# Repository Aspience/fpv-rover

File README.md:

# FPV Rover

Monorepo for an FPV rover (LEGO Audi e-tron) controlled from a web UI with live video, telemetry OSD, and optional physical gamepad input.

## Contents

- [Overview](#overview)
- [Hardware requirements](#hardware-requirements)
- [KiCad project](#kicad-project)
- [Software requirements](#software-requirements)
- [Installation and updates](#installation-and-updates)
  - [Prerequisites on the Pi](#prerequisites-on-the-pi)
  - [First install (bootstrap)](#first-install-bootstrap)
  - [Updating to a new version](#updating-to-a-new-version)
- [Technical reference](#technical-reference)
  - [Repository structure](#repository-structure)
  - [Backend modules](#backend-modules)
  - [Environment variables](#environment-variables)
  - [Local development](#local-development)
  - [Backend ↔ frontend sync](#backend--frontend-sync)
  - [Infra / Docker](#infra--docker)
  - [Releasing a new version](#releasing-a-new-version)
  - [Boot persistence (optional)](#boot-persistence-optional)

---

## Overview

The project follows a **modular architecture**: each hardware capability (motion, power, thermal, IMU, light, camera, gamepad) is an independent backend module under `backend/modules/<name>/`. Gamepads connect over USB or **Bluetooth** (the `bluetooth` module handles wireless pairing; `gamepad` reads input via evdev). Modules are toggled at runtime via `ROVER_MODULES_*` feature flags in `.env` — only enabled modules are loaded, initialized, and exposed to the UI.

This design lets you **mix and match hardware configurations** without changing application code. A minimal bench setup might enable only `camera` and `motion`; a fully instrumented rover can enable every sensor. The frontend reads module flags from `GET /config` on startup and shows or hides controls accordingly.

The stack runs on **Raspberry Pi** (reference build: Pi Zero 2 W) inside Docker Compose: FastAPI backend, React SPA, nginx reverse proxy, MediaMTX for WebRTC video, and a pigpio sidecar for GPIO/PWM motor control.

---

## Hardware requirements

The reference rover is built around a **Raspberry Pi** (64-bit). Peripherals connect over the buses listed below.

| Component | Module / role | Bus / interface |
|-----------|---------------|-----------------|
| **Raspberry Pi Zero 2 W** (or compatible Pi 3/4/5) | Host — runs Docker stack | — |
| **Arducam IMX462** (Pivariety) | FPV camera, night mode | **CSI-2** → libcamera / V4L2 (`/dev/video0`) |
| **GY-302** (BH1750) | Ambient light sensor; triggers camera night mode below threshold | **I2C** (default address `0x23`) |
| **DS18B20** | Temperature sensors (motors, BMS, BEC, charger) | **1-Wire** (default GPIO 4 via `dtoverlay=w1-gpio`) |
| **TB6612FNG** × 3 | Motor drivers — front drive, rear drive, steering (LEGO Control+ hubs) | **GPIO / PWM** via pigpio daemon; encoder tachos on GPIO |
| **GY-521** (MPU6050) | Gyroscope + accelerometer (orientation OSD) | **I2C** (default address `0x68`) |
| **INA219** | Battery voltage and current monitoring | **I2C** (default address `0x40`) |
| **BMS 2S** battery charge controller | 2S Li-ion pack — **2P2S** layout (four 18650 cells) | Passive power path; temperature via DS18B20 on 1-Wire |
| **iFlight Micro 2–8S BEC** | Switched regulator — 5 V supply for the Pi | Power only (no data bus) |
| **TOF400C** | Laser ToF distance sensor | **I2C** (planned; not yet implemented in software) |
| **Gamepad** (USB or Bluetooth) | Physical input (optional); **Bluetooth** is used to pair wireless controllers, then input is read via evdev | **Bluetooth** (pairing, host netns via `nsenter`) → **evdev** (`/dev/input/event*`) |

### Host interfaces to enable

Before deployment, enable these on the Pi (see [Prerequisites on the Pi](#prerequisites-on-the-pi)):

| Interface | Used by |
|-----------|---------|
| I2C (`/dev/i2c-1`) | INA219, BH1750, MPU6050, TOF400C |
| 1-Wire (`/sys/bus/w1`) | DS18B20 |
| GPIO / pigpio (`/dev/gpiochip0`) | TB6612FNG motor drivers |
| CSI camera + Arducam overlay | IMX462 |
| Bluetooth | Gamepad pairing (wireless controllers) |
| evdev (`/dev/input`) | Gamepad input (USB and paired Bluetooth) |

Motion and gamepad modules require the **pigpiod** Docker sidecar. Without pigpio or when the daemon is unreachable, motion falls back to mock hardware (useful for local dev).

---

## KiCad project

Electrical design lives in [`hardware/`](hardware/) as a **KiCad 10** project. The schematic captures the wiring described in [`SCHEMA.md`](SCHEMA.md) (main board + expansion board buses, power path, motor drivers, sensors); `SCHEMA.md` remains the physical wiring source of truth.

| File | What it is |
|------|------------|
| `hardware/fpv-rover.kicad_pro` | KiCad project — open this in KiCad |
| `hardware/fpv-rover.kicad_sch` | Schematic (editable source) |
| `hardware/fpv-rover.kicad_pcb` | PCB layout (placeholder — build uses perfboard, see `SCHEMA.md`) |
| `hardware/fpv-rover-schematic.pdf` | Exported schematic — view without KiCad |
| `hardware/fpv-rover-schematic.svg` / `.png` | Same schematic as vector / raster image |

To view the design, open the PDF/SVG exports. To edit, open `fpv-rover.kicad_pro` in [KiCad](https://www.kicad.org/) 10+ and re-export the PDF/SVG afterwards so the rendered files stay in sync.

---

## Software requirements

| Requirement | Notes |
|-------------|-------|
| **Linux 64-bit** | Required for production images and MediaMTX arm64 build |
| **Raspberry Pi OS Lite 64-bit** (recommended) | Bookworm or Trixie; Bullseye supported on Pi 4 and older |
| **Docker Engine** + **Docker Compose** plugin | Production deployment and OTA updates |
| **git**, **curl** | Bootstrap and OTA scripts |

For local development on any OS: Python 3.12+ with [uv](https://docs.astral.sh/uv/), Node.js 20+ for the frontend.

---

## Installation and updates

On Raspberry Pi, backend, frontend, and mediamtx images are built in GitHub Actions (arm64) and pulled at runtime — no local `npm run build` or `docker compose build` on the device.

### Prerequisites on the Pi

Bootstrap requires **git**, **curl**, **Docker**, and the **Docker Compose** plugin. On a fresh Raspberry Pi OS image these are often missing.

#### 1. Git and curl

```bash
sudo apt update
sudo apt install -y git curl
```

#### 2. Docker and Docker Compose

```bash
curl -fsSL https://get.docker.com | sh
sudo usermod -aG docker "$USER"
newgrp docker
```

Log out and back in (or run `newgrp docker`) so your user can run Docker without `sudo`.

Verify:

```bash
docker --version
docker compose version
docker ps
```

#### 3. I2C and 1-Wire

Backend expects `/dev/i2c-1` and `/sys/bus/w1` on the host. Enable both before bootstrap — sensors do not need to be connected yet.

```bash
sudo raspi-config
# Interface Options → I2C → Enable
# Interface Options → 1-Wire → Enable
sudo reboot
```

Or add to `/boot/firmware/config.txt` (older images: `/boot/config.txt`):

```
dtparam=i2c_arm=on
dtoverlay=w1-gpio,gpiopin=4
```

After reboot, verify:

```bash
ls /dev/i2c-1
ls /sys/bus/w1
```

`gpiopin=4` matches the default `ROVER_W1_GPIO=4` in `.env.example`.

#### 4. Arducam IMX462 camera drivers

The IMX462 is an **Arducam Pivariety** module. It requires Arducam's custom libcamera stack and a device-tree overlay on the host (outside Docker). Follow the [Arducam Pivariety Quick Start Guide](https://docs.arducam.com/Raspberry-Pi-Camera/Pivariety-Camera/Quick-Start-Guide/).

**Step 1 — download the install script:**

```bash
wget -O install_pivariety_pkgs.sh https://github.com/ArduCAM/Arducam-Pivariety-V4L2-Driver/releases/download/install_script/install_pivariety_pkgs.sh
chmod +x install_pivariety_pkgs.sh
```

**Step 2 — install Arducam libcamera (on the Pi host, before or after bootstrap):**

```bash
./install_pivariety_pkgs.sh -p libcamera_dev
./install_pivariety_pkgs.sh -p libcamera_apps
```

No reboot yet — proceed to Step 3.

**Step 3 — enable the camera overlay** in `/boot/firmware/config.txt` (Pi 4/5 Bookworm/Trixie; older images may use `/boot/config.txt`):

```
camera_auto_detect=0
dtoverlay=arducam-pivariety
```

On Pi 5 / CM5 with the camera on the **CAM0** port, use `dtoverlay=arducam-pivariety,cam0` instead.

Save and reboot:

```bash
sudo reboot
```

**Verify** after reboot:

```bash
rpicam-still --list-cameras    # Bookworm / Trixie
# or: libcamera-still --list-cameras   # Bullseye
ls /dev/video0
```

The MediaMTX container ships with Arducam libcamera libraries baked in ([`infra/mediamtx/Dockerfile`](infra/mediamtx/Dockerfile)); the **host overlay and libcamera packages** are still required for the camera device node to appear.

> If you see `Configuration file 'arducam-pivariety.json' not found for IPA module 'rpi/pisp'`, it can be safely ignored — the config is embedded in camera firmware.

#### 5. SSH deploy key

Bootstrap can generate one interactively, or configure manually:

```bash
ssh-keygen -t ed25519 -f ~/.ssh/fpv_rover_deploy -N ""
cat ~/.ssh/fpv_rover_deploy.pub
```

Add the public key in GitHub → **Settings → Deploy keys** (read-only).

`~/.ssh/config`:

```sshconfig
Host github.com
  IdentityFile ~/.ssh/fpv_rover_deploy
  IdentitiesOnly yes
```

#### 6. GHCR login (only if images are private)

```bash
echo "$GITHUB_PAT" | docker login ghcr.io -u YOUR_GITHUB_USER --password-stdin
```

PAT needs `read:packages`. Public GHCR packages do not require login.

### First install (bootstrap)

```bash
sudo mkdir -p /opt/fpv-rover && sudo chown "$USER" /opt/fpv-rover
git clone git@github.com:Aspience/fpv-rover.git /opt/fpv-rover
cd /opt/fpv-rover
./scripts/bootstrap.sh --enable-systemd
# or pin a release tag:
./scripts/bootstrap.sh --tag v0.1.5 --enable-systemd
```

Bootstrap creates `.env` from `.env.example` with production values (`ROVER_OTA_ENABLED=true`, `VITE_RPI_HOST`, `IMAGE_TAG`, etc.). It does **not** create `.env.local`.

Before pulling images, bootstrap **pauses** so you can edit env interactively (opens `${EDITOR:-nano}` on request). Set module flags, confirm `VITE_RPI_HOST`, and optionally create `.env.local` for hardware IDs — then press Enter to continue.

Example `.env.local` (do **not** copy the full `.env.example` — `.env.local` overrides `.env` and would reset OTA settings to example defaults):

```
ROVER_MODULES_MOTION_ENABLED=true
ROVER_MODULES_GAMEPAD_ENABLED=true
ROVER_MODULES_CAMERA_ENABLED=true
ROVER_THERMAL_SENSOR_IDS={"motor_steering":"28-..."}
```

Use `--non-interactive` to skip the env edit pause when env is preconfigured.

#### Bootstrap options

| Flag | Default | Description |
|------|---------|-------------|
| `--install-dir PATH` | `/opt/fpv-rover` | Install path on the device |
| `--tag TAG` | `latest` (or `$IMAGE_TAG`) | Git tag and Docker image tag to deploy |
| `--repo URL` | `git@github.com:Aspience/fpv-rover.git` | Git remote for clone/fetch |
| `--non-interactive` | off | Fail fast if SSH/GitHub/GHCR setup is missing |
| `--skip-clone` | off | Skip clone when repo is already in `--install-dir` |
| `--skip-ssh` | off | Skip SSH key generation and GitHub deploy-key prompt |
| `--skip-ghcr-login` | off | Skip `docker login ghcr.io` |
| `--skip-deploy` | off | Setup only (env, clone) — no `compose pull/up` |
| `--enable-systemd` | off | Install and enable `infra/systemd/fpv-rover.service` |
| `--quiet` | off | Less stdout; log file stays verbose |

| Env var | Used for |
|---------|----------|
| `VITE_RPI_HOST` | Browser-facing Pi IP/hostname (non-interactive bootstrap) |
| `IMAGE_TAG` | Default tag when `--tag` is omitted |
| `GHCR_USER` + `GHCR_TOKEN` | Optional GHCR login (public packages skip this) |

**Logs:** `/opt/fpv-rover/logs/bootstrap.log`

```bash
tail -100 /opt/fpv-rover/logs/bootstrap.log
```

### Updating to a new version

#### From the UI

Open **Settings** → **Check for updates** → **Install update**. The UI shows a fullscreen overlay while the rover restarts and polls `GET /health` every 3 seconds until the backend is back.

Requires `ROVER_OTA_ENABLED=true` (set by bootstrap on production installs).

#### Manual update / rollback (OTA script)

```bash
cd /opt/fpv-rover
./scripts/ota_update.sh v0.2.0        # upgrade (prompts for confirmation)
./scripts/ota_update.sh v0.1.0        # rollback (prompts for confirmation)
./scripts/ota_update.sh v0.2.0 --yes  # skip the confirmation prompt
```

The script waits 3 seconds (so the API can respond), fetches the git tag, resolves per-service image tags from `image-tags.env` (with nearest-tag fallback for older releases), pulls Docker images, and runs `docker compose up -d`. It never overwrites `.env` or `.env.local`.

Before any destructive step the script asks:

```text
Update from v0.1.0 to v0.2.0? [y/N]
```

The prompt is skipped when running non-interactively (backend OTA API), with `--yes`/`-y`, or when `ROVER_OTA_ASSUME_YES=1`.

**Logs:** `/opt/fpv-rover/logs/ota.log`

```bash
tail -100 /opt/fpv-rover/logs/ota.log
```

---

## Technical reference

### Repository structure

```
fpv-rover/
├── backend/          # Python — FastAPI, hardware modules, WebSocket
│   ├── api/          # REST routes, WebSocket handler, command/telemetry schemas
│   ├── core/         # Settings, event bus, module registry, startup
│   ├── modules/      # Pluggable hardware modules (see below)
│   └── tests/
├── frontend/         # React SPA — live video, OSD, motion levers, settings
├── infra/            # Nginx reverse proxy, MediaMTX, systemd unit
├── scripts/          # Bootstrap and OTA update scripts
├── .env.example      # Shared environment template (backend + frontend)
└── docker-compose.yml
```

Each backend module typically has `*.module.py`, `*.schema.py`, `*.config.py`, and optional `*.utils.py` / `*.service.py`.

### Backend modules

| Module | Role |
|--------|------|
| `motion` | LEGO Control+ drive (front/rear) + steering via TB6612FNG + pigpio; PID closed loop, homing calibration |
| `gamepad` | Physical gamepad over Linux evdev (`/dev/input`); maps to motion commands |
| `power` | INA219 battery monitoring (I2C) |
| `thermal` | DS18B20 temperature sensors (1-Wire) |
| `imu` | MPU6050 orientation (I2C) |
| `light` | BH1750 ambient lux (I2C); triggers camera night mode below threshold |
| `camera` | MediaMTX integration — recording and stream config |
| `bluetooth` | Bluetooth gamepad pairing (host netns via `nsenter`) |

When `ROVER_MODULES_MOTION_ENABLED=true`, the backend runs **steering calibration automatically** on startup (`core/startup.py`). Physical gamepad input requires both `ROVER_MODULES_GAMEPAD_ENABLED` and `ROVER_MODULES_MOTION_ENABLED`.

Motion tuning constants (PID loop rate, homing power, throttle limits) live in `motion.config.py`. Gamepad evdev codes and poll intervals — in `gamepad.config.py`. GPIO pins, PID gains, and speed limits are runtime settings via `ROVER_*` env.

### Environment variables

Both backend and frontend read from a **single root `.env` file**:

```bash
cp .env.example .env
```

On the Pi or in Docker, optional `.env.local` overrides `.env` without touching git-tracked files.

#### Feature flags

| Variable | Default | Description |
|----------|---------|-------------|
| `ROVER_MODULES_POWER_ENABLED` | `false` | INA219 power module |
| `ROVER_MODULES_MOTION_ENABLED` | `false` | Motion module (LEGO Control+ + TB6612FNG) |
| `ROVER_MODULES_GAMEPAD_ENABLED` | `false` | Physical gamepad via evdev |
| `ROVER_MODULES_THERMAL_ENABLED` | `false` | DS18B20 thermal module |
| `ROVER_MODULES_IMU_ENABLED` | `false` | MPU6050 IMU module |
| `ROVER_MODULES_LIGHT_ENABLED` | `false` | BH1750 light module |
| `ROVER_MODULES_CAMERA_ENABLED` | `false` | MediaMTX camera integration |
| `ROVER_MODULES_BLUETOOTH_ENABLED` | `false` | Bluetooth gamepad pairing |

Backend loads `ROVER_*` via pydantic-settings (`backend/core/config.py`).  
Frontend loads `VITE_*` via Vite with `envDir` pointing at the repo root (`frontend/vite.config.ts`).

> **Note:** `VITE_*` variables are embedded at **build time**. After changing them, rebuild the frontend (`npm run build` or `docker compose build frontend`).

#### Motion & pigpio

| Variable | Default | Description |
|----------|---------|-------------|
| `ROVER_PIGPIO_HOST` | `pigpiod` | pigpio daemon hostname (Docker service name) |
| `ROVER_PIGPIO_PORT` | `8888` | pigpio daemon TCP port |
| `ROVER_MOTION_FRONT_PWMA_GPIO` | `18` | Front drive — PWM pin (TB6612FNG PWMA) |
| `ROVER_MOTION_FRONT_AIN1_GPIO` | `23` | Front drive — direction AIN1 |
| `ROVER_MOTION_FRONT_AIN2_GPIO` | `24` | Front drive — direction AIN2 |
| `ROVER_MOTION_FRONT_TACHO_A_GPIO` | `17` | Front drive — encoder channel A |
| `ROVER_MOTION_FRONT_TACHO_B_GPIO` | `27` | Front drive — encoder channel B |
| `ROVER_MOTION_REAR_PWMA_GPIO` | `12` | Rear drive — PWM pin |
| `ROVER_MOTION_REAR_AIN1_GPIO` | `16` | Rear drive — direction AIN1 |
| `ROVER_MOTION_REAR_AIN2_GPIO` | `20` | Rear drive — direction AIN2 |
| `ROVER_MOTION_REAR_TACHO_A_GPIO` | `5` | Rear drive — encoder channel A |
| `ROVER_MOTION_REAR_TACHO_B_GPIO` | `6` | Rear drive — encoder channel B |
| `ROVER_MOTION_STEER_PWMA_GPIO` | `13` | Steering — PWM pin |
| `ROVER_MOTION_STEER_AIN1_GPIO` | `19` | Steering — direction AIN1 |
| `ROVER_MOTION_STEER_AIN2_GPIO` | `26` | Steering — direction AIN2 |
| `ROVER_MOTION_STEER_TACHO_A_GPIO` | `21` | Steering — encoder channel A |
| `ROVER_MOTION_STEER_TACHO_B_GPIO` | `22` | Steering — encoder channel B |
| `ROVER_MOTION_MAX_SPEED_TICKS` | `800` | Max drive speed in encoder ticks/s at full throttle |
| `ROVER_MOTION_STEER_MAX_DEG` | `45` | Maximum steering angle (°) |
| `ROVER_MOTION_PID_KP` | `0.8` | PID proportional gain |
| `ROVER_MOTION_PID_KI` | `0.05` | PID integral gain |
| `ROVER_MOTION_PID_KD` | `0.01` | PID derivative gain |

#### Global backend

| Variable | Default | Description |
|----------|---------|-------------|
| `ROVER_LOG_LEVEL` | `INFO` | Logging level |
| `ROVER_HOST` | `0.0.0.0` | FastAPI bind address |
| `ROVER_PORT` | `8000` | FastAPI port |
| `ROVER_I2C_BUS` | `1` | Linux I2C bus number |
| `ROVER_W1_GPIO` | `4` | 1-Wire GPIO pin (must match `dtoverlay=w1-gpio`) |
| `ROVER_WS_TELEMETRY_HZ` | `20` | WebSocket telemetry broadcast rate (Hz) |
| `ROVER_HEARTBEAT_TIMEOUT_SEC` | `1.0` | Watchdog heartbeat timeout |
| `ROVER_IO_RETRY_DELAY_SEC` | `2.0` | Hardware I/O retry delay |

#### MediaMTX

| Variable | Default | Description |
|----------|---------|-------------|
| `ROVER_MEDIAMTX_API_URL` | `http://mediamtx:9997` | MediaMTX control API |
| `ROVER_MEDIAMTX_RECORD_START_PATH` | `/v3/recordings/start/{stream_path}` | Start recording API path template |
| `ROVER_MEDIAMTX_RECORD_STOP_PATH` | `/v3/recordings/stop/{stream_path}` | Stop recording API path template |
| `ROVER_MEDIAMTX_STREAM_CONFIG_PATH` | `/v3/config/paths/patch/{stream_path}` | Patch stream config path template |
| `ROVER_MEDIAMTX_STREAM_CONFIG_GET_PATH` | `/v3/config/paths/get/{stream_path}` | Get stream config path template |

#### Hardware addresses & devices

| Variable | Default | Description |
|----------|---------|-------------|
| `ROVER_POWER_I2C_ADDRESS` | `0x40` | INA219 I2C address |
| `ROVER_IMU_I2C_ADDRESS` | `0x68` | MPU6050 I2C address |
| `ROVER_LIGHT_I2C_ADDRESS` | `0x23` | BH1750 I2C address |
| `ROVER_W1_BASE_PATH` | `/sys/bus/w1/devices` | 1-Wire sysfs base path |
| `ROVER_THERMAL_W1_SLAVE_FILE` | `w1_slave` | Filename inside each sensor directory |
| `ROVER_THERMAL_SENSOR_IDS` | *(JSON map)* | DS18B20 ROM IDs keyed by sensor name |
| `ROVER_CAMERA_V4L2_DEVICE` | `/dev/video0` | Camera V4L2 device |
| `ROVER_CAMERA_V4L2_CTL_BIN` | `v4l2-ctl` | Path to `v4l2-ctl` binary |
| `ROVER_CAMERA_STREAM_PATH` | `rover` | MediaMTX stream path name |

#### Frontend (build-time)

| Variable | Default | Description |
|----------|---------|-------------|
| `VITE_RPI_HOST` | `localhost` | Dev server proxy target; production WebRTC fallback |
| `VITE_API_PORT` | `8000` | Dev server proxy target for REST/WebSocket |
| `VITE_WEBRTC_PORT` | `8889` | MediaMTX WebRTC (WHEP) port in the browser |

#### Docker / OTA (production)

| Variable | Default | Description |
|----------|---------|-------------|
| `ROVER_OTA_ENABLED` | `false` | Allow `POST /update/apply` (set `true` on Pi) |
| `ROVER_OTA_INSTALL_DIR` | `/opt/fpv-rover` | Install path on the device |
| `ROVER_OTA_SCRIPT` | `/opt/fpv-rover/scripts/ota_update.sh` | Update script path |
| `ROVER_OTA_SSH_KEY_PATH` | *(empty)* | Deploy key path; bootstrap sets `$HOME/.ssh/fpv_rover_deploy` |
| `ROVER_OTA_ASSUME_YES` | *(empty)* | Set `1`/`true` to skip manual-update confirmation |
| `ROVER_GITHUB_OWNER` | `aspience` | GitHub owner for release check and GHCR image path |
| `ROVER_GITHUB_REPO` | `fpv-rover` | GitHub repo for release check and GHCR image path |
| `ROVER_GITHUB_TOKEN` | *(empty)* | Optional PAT for GitHub API rate limits |
| `FPV_ROVER_IMAGE_REGISTRY` | `ghcr.io` | Container registry for production images |
| `IMAGE_TAG` | `latest` | Target release tag for git checkout and app version |
| `BACKEND_IMAGE_TAG` | *(auto)* | Pin backend image tag — override in `.env.local` |
| `FRONTEND_IMAGE_TAG` | *(auto)* | Pin frontend image tag — override in `.env.local` |
| `MEDIAMTX_IMAGE_TAG` | *(auto)* | Pin mediamtx image tag — override in `.env.local` |

> **Per-service tag precedence:** on deploy/OTA, tags are resolved as (1) explicit pin in `.env.local`, then (2) `image-tags.env` from the checked-out release, then (3) nearest existing GHCR tag. To pin a specific service tag, put it in `.env.local` (not `.env`, which the OTA script rewrites).

Compose also uses `PIGPIOD_IMAGE` (default `zinen2/alpine-pigpiod:pigpio-v79`) for the GPIO sidecar.

Production images are pulled from `${FPV_ROVER_IMAGE_REGISTRY}/${ROVER_GITHUB_OWNER}/${ROVER_GITHUB_REPO}-{backend,frontend,mediamtx}`.

### Local development

#### Backend

```bash
uv sync --project backend
uv run --project backend pytest
uv run --project backend ruff check
uv run --project backend ruff format
uv run --project backend fpv-rover
```

API: `http://localhost:8000` — OpenAPI docs at `/docs`.

Install pre-commit hooks (from repo root):

```bash
uv run --project backend pre-commit install
```

#### Frontend

React 19 SPA: live video (WebRTC), telemetry OSD, on-screen throttle/steer levers, keyboard shortcuts, light and camera controls. Physical gamepads are handled on the **backend** (evdev).

**Stack:** React 19, TypeScript, Vite 8, Tailwind CSS 4, Zustand, Zod, Axios.

```bash
cd frontend
npm ci
npm run dev          # http://localhost:5173
npm run build        # production bundle → dist/
npm run lint
npm run preview
```

Run backend and frontend in separate terminals:

```bash
# terminal 1
uv run --project backend fpv-rover

# terminal 2
cd frontend && npm run dev
```

Vite proxies `/api` and `/ws` to the backend using `VITE_RPI_HOST` and `VITE_API_PORT`.

### Backend ↔ frontend sync

The UI talks to the backend over three channels. Keep their contracts aligned when you change either side.

#### 1. Shared configuration (`.env`)

Module flags (`ROVER_MODULES_*`) are exposed via `GET /config`; the frontend fetches them on startup.

When deploying on a Pi or via Docker, REST and WebSocket use nginx on port 80 (`/api`, `/ws`). WebRTC/WHEP uses `window.location.hostname` and `VITE_WEBRTC_PORT` (not proxied through nginx).

#### 2. REST — module flags

| | Backend | Frontend |
|---|---------|----------|
| Endpoint | `GET /config` | `fetchConfig()` in `frontend/src/api/http.ts` |
| Schema | `backend/core/schemas/config.py` → `ConfigResponse` | `frontend/src/types/schemas.ts` → `ConfigResponseSchema` |
| Types | OpenAPI (`/openapi.json`) | `frontend/src/types/contracts.ts` |

**After changing the REST API:**

1. Update Pydantic models in `backend/modules/<name>/<name>.schema.py` or `backend/core/schemas/`.
2. Run `uv run --project backend pytest`.
3. Mirror the shape in `frontend/src/types/schemas.ts` (Zod) and `frontend/src/types/contracts.ts`.
4. Optionally regenerate REST types (backend must be running): `cd frontend && npm run generate:api`

#### 3. WebSocket — telemetry and commands

| | Backend | Frontend |
|---|---------|----------|
| Endpoint | `WS /ws` | `frontend/src/api/websocket.ts` |
| Server → client | `backend/modules/<name>/<name>.schema.py`, `backend/api/schemas/telemetry.py` | `TelemetryMessageSchema`, `ErrorMessageSchema` |
| Client → server | `backend/api/schemas/commands.py` | `ClientCommandSchema` |

**Message types:**

- **Telemetry** (default 20 Hz): `{ type: "telemetry", modules: { power?, motion?, light?, thermal?, imu?, bluetooth?, gamepad? } }`
- **Commands (frontend):** `heartbeat` (every 500 ms), `move`, `calibrate`, `set_brightness`
- **Commands (backend only today):** `record` — not yet sent from the UI
- **Errors:** `{ type: "error", message: string }`

Motion control from the UI, keyboard, or physical gamepad converges on the same backend path. Use `GET /ws-protocol` on a running backend to inspect documented JSON shapes.

> **Note:** `STEER_MAX_DEG` in `frontend/src/constants.ts` is hardcoded (default 45°). Keep it aligned with `ROVER_MOTION_STEER_MAX_DEG` when you change steering limits.

#### 4. Video — WebRTC (WHEP)

Video does not go through FastAPI. MediaMTX serves the stream; the frontend connects via WHEP:

- Stream path: `rover` (see `infra/mediamtx/mediamtx.yml`)
- Frontend: `POST http://{host}:{VITE_WEBRTC_PORT}/rover/whep`
- Backend camera module controls recording via `ROVER_MEDIAMTX_API_URL`

Keep `VITE_WEBRTC_PORT` aligned with MediaMTX `webrtcAddress` (default **8889**).

#### Sync checklist

When you add or change an API field:

- [ ] Pydantic model in `backend/modules/<name>/<name>.schema.py` (or `backend/api/schemas/`)
- [ ] Zod schema in `frontend/src/types/schemas.ts`
- [ ] TypeScript interface in `frontend/src/types/contracts.ts` (if applicable)
- [ ] Backend tests (`pytest`)
- [ ] Manual check: backend running + `npm run dev` or built frontend

### Infra / Docker

```bash
cp .env.example .env
docker compose up --build
```

| Service | Port(s) | Role |
|---------|---------|------|
| `pigpiod` | 8888 (internal) | pigpio daemon — GPIO/PWM for motion motors |
| `backend` | 8000 | FastAPI, hardware modules |
| `frontend` | 3000 | Static SPA (Caddy) |
| `nginx` | 80 | Reverse proxy: `/` → frontend, `/api/` and `/ws` → backend |
| `mediamtx` | 8554, 8889, 8189/udp, 9997 | RTSP, WebRTC, ICE UDP, control API (Arducam/Pivariety libcamera) |

Pi device mounts in [`docker-compose.yml`](docker-compose.yml): `/dev/i2c-1`, `/dev/video0`, `/dev/input` (gamepad), `/sys/bus/w1` (1-Wire), `/dev/gpiochip0` (pigpiod sidecar).

Production UI on port 80: REST → `/api`, WebSocket → `/ws`. WebRTC/WHEP → `http://<pi-ip>:8889/rover/whep`.

Locally, `mediamtx` is built from [`infra/mediamtx/Dockerfile`](infra/mediamtx/Dockerfile); production pulls a pre-built image from GHCR.

### Releasing a new version

```bash
git tag v0.2.0
git push origin v0.2.0
```

GitHub Actions (`.github/workflows/release.yml`) builds arm64 backend, frontend, and mediamtx images and pushes them to GHCR. Each service is rebuilt **only when its context changed** since the previous `v*` tag. Skipped services keep their previous image tag.

The workflow writes `image-tags.env` with resolved tags per service. Release assets include `image-tags.env`, compose files, `infra/**/*`, OTA/bootstrap scripts, and `.env.example`.

### Boot persistence (optional)

Bootstrap can install the systemd unit with `--enable-systemd`, or manually:

```bash
sudo cp infra/systemd/fpv-rover.service /etc/systemd/system/
sudo systemctl enable --now fpv-rover
```

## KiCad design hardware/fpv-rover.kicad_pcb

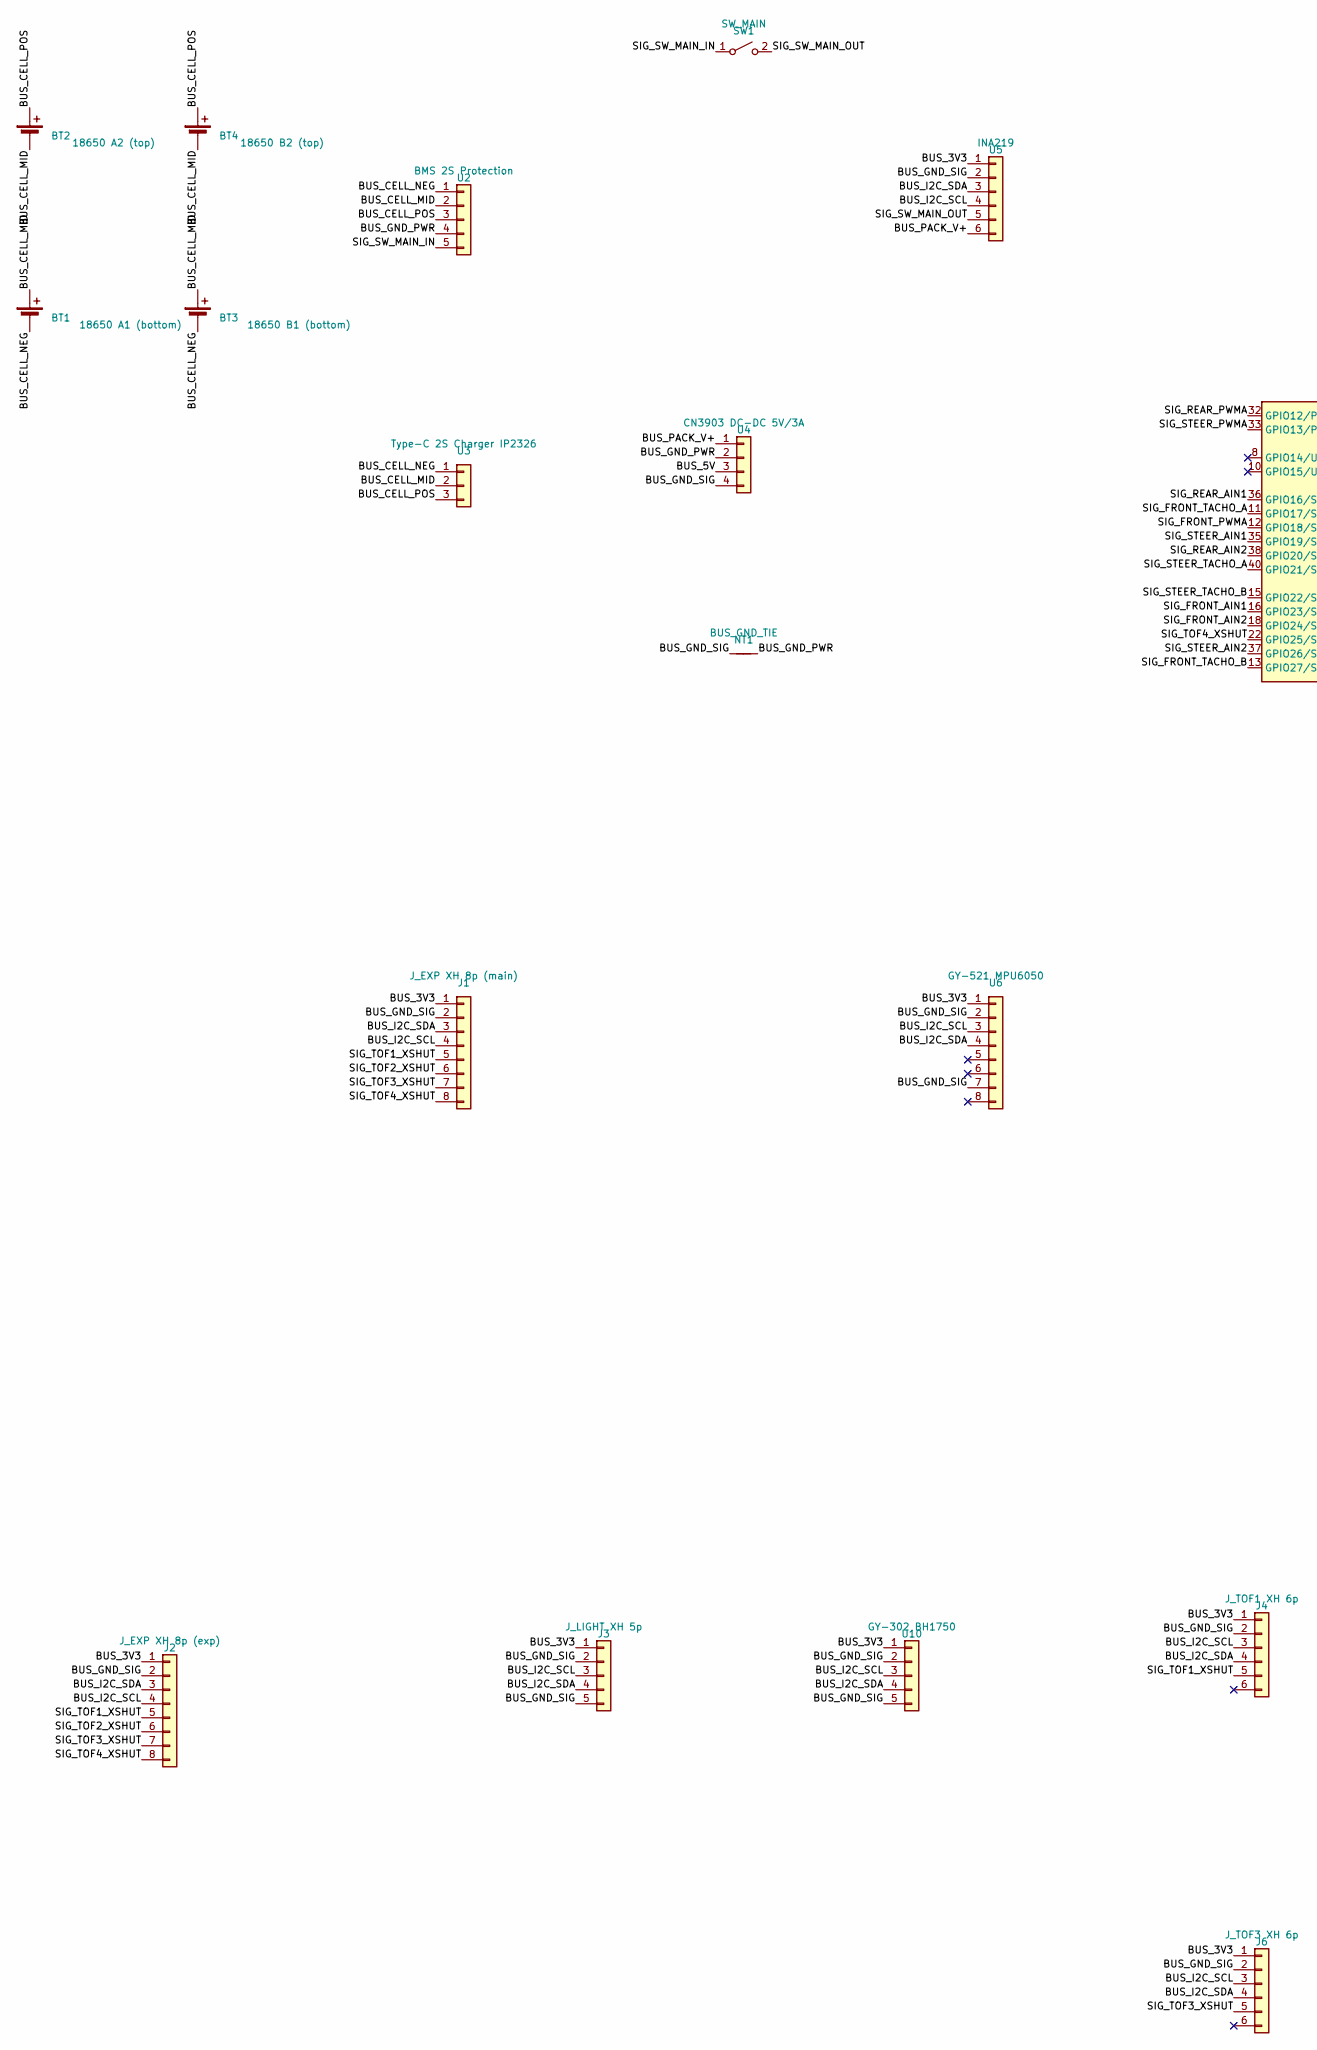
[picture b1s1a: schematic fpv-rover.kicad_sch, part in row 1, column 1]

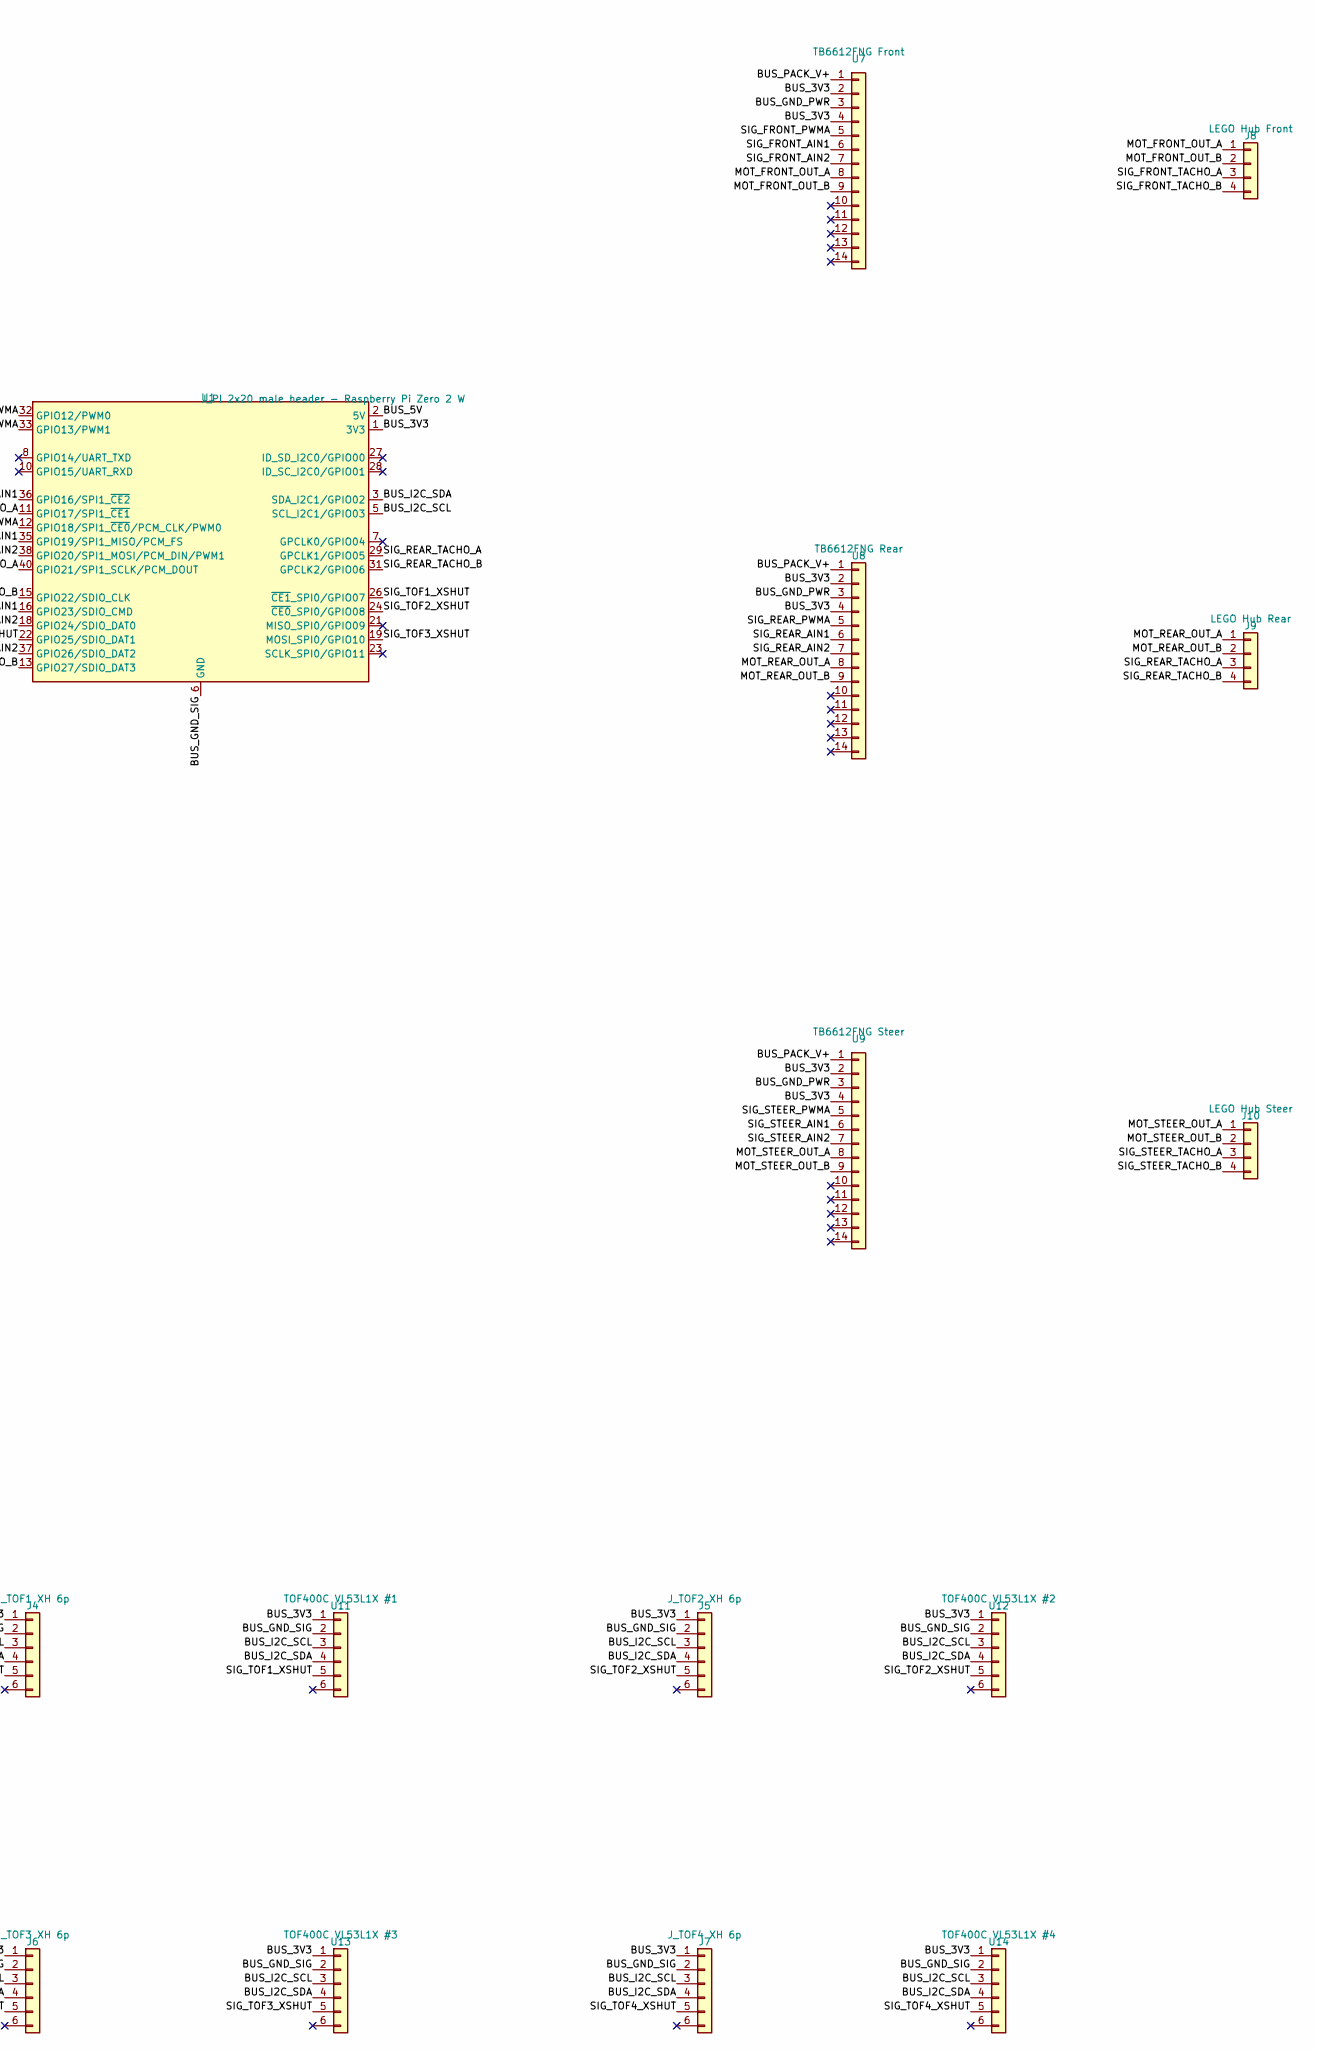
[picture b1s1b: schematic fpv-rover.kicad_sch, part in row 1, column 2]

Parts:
BT1: 18650 A1 (bottom); PinHeader_1x02_P2.54mm_Vertical
BT2: 18650 A2 (top); PinHeader_1x02_P2.54mm_Vertical
BT3: 18650 B1 (bottom); PinHeader_1x02_P2.54mm_Vertical
BT4: 18650 B2 (top); PinHeader_1x02_P2.54mm_Vertical
J1: J_EXP XH 8p (main); JST_XH_B8B-XH-A_1x08_P2.50mm_Vertical
J2: J_EXP XH 8p (exp); JST_XH_B8B-XH-A_1x08_P2.50mm_Vertical
J3: J_LIGHT XH 5p; JST_XH_B5B-XH-A_1x05_P2.50mm_Vertical
J4: J_TOF1 XH 6p; JST_XH_B6B-XH-A_1x06_P2.50mm_Vertical
J5: J_TOF2 XH 6p; JST_XH_B6B-XH-A_1x06_P2.50mm_Vertical
J6: J_TOF3 XH 6p; JST_XH_B6B-XH-A_1x06_P2.50mm_Vertical
J7: J_TOF4 XH 6p; JST_XH_B6B-XH-A_1x06_P2.50mm_Vertical
J8: LEGO Hub Front; JST_XH_B4B-XH-A_1x04_P2.50mm_Vertical
J9: LEGO Hub Rear; JST_XH_B4B-XH-A_1x04_P2.50mm_Vertical
J10: LEGO Hub Steer; JST_XH_B4B-XH-A_1x04_P2.50mm_Vertical
NT1: BUS_GND_TIE; NetTie-2_THT_Pad1.0mm
SW1: SW_MAIN; PinHeader_1x02_P2.54mm_Vertical
U1: J_PI 2x20 male header - Raspberry Pi Zero 2 W; PinHeader_2x20_P2.54mm_Vertical
U2: BMS 2S Protection; PinHeader_1x05_P2.54mm_Vertical
U3: Type-C 2S Charger IP2326; PinHeader_1x03_P2.54mm_Vertical
U4: CN3903 DC-DC 5V/3A; PinHeader_1x04_P2.54mm_Vertical
U5: INA219; PinHeader_1x06_P2.54mm_Vertical
U6: GY-521 MPU6050; PinHeader_1x08_P2.54mm_Vertical
U7: TB6612FNG Front; PinHeader_1x14_P2.54mm_Vertical
U8: TB6612FNG Rear; PinHeader_1x14_P2.54mm_Vertical
U9: TB6612FNG Steer; PinHeader_1x14_P2.54mm_Vertical
U10: GY-302 BH1750; PinHeader_1x05_P2.54mm_Vertical
U11: TOF400C VL53L1X #1; PinHeader_1x06_P2.54mm_Vertical
U12: TOF400C VL53L1X #2; PinHeader_1x06_P2.54mm_Vertical
U13: TOF400C VL53L1X #3; PinHeader_1x06_P2.54mm_Vertical
U14: TOF400C VL53L1X #4; PinHeader_1x06_P2.54mm_Vertical

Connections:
BUS_3V3: J1.1, J2.1, J3.1, J4.1, J5.1, J6.1, J7.1, U1.1 (3V3), U1.17 (3V3), U5.1, U6.1, U7.2, U7.4, U8.2, U8.4, U9.2, U9.4, U10.1, U11.1, U12.1, U13.1, U14.1
BUS_5V: U1.2 (5V), U1.4 (5V), U4.3
BUS_CELL_MID: BT1.1 (+), BT2.2 (-), BT3.1 (+), BT4.2 (-), U2.2, U3.2
BUS_CELL_NEG: BT1.2 (-), BT3.2 (-), U2.1, U3.1
BUS_CELL_POS: BT2.1 (+), BT4.1 (+), U2.3, U3.3
BUS_GND_PWR: NT1.2, U2.4, U4.2, U7.3, U8.3, U9.3
BUS_GND_SIG: J1.2, J2.2, J3.2, J3.5, J4.2, J5.2, J6.2, J7.2, NT1.1, U1.6 (GND), U1.9 (GND), U1.14 (GND), U1.20 (GND), U1.25 (GND), U1.30 (GND), U1.34 (GND), U1.39 (GND), U4.4, U5.2, U6.2, U6.7, U10.2, U10.5, U11.2, U12.2, U13.2, U14.2
BUS_I2C_SCL: J1.4, J2.4, J3.3, J4.3, J5.3, J6.3, J7.3, U1.5 (SCL_I2C1/GPIO03), U5.4, U6.3, U10.3, U11.3, U12.3, U13.3, U14.3
BUS_I2C_SDA: J1.3, J2.3, J3.4, J4.4, J5.4, J6.4, J7.4, U1.3 (SDA_I2C1/GPIO02), U5.3, U6.4, U10.4, U11.4, U12.4, U13.4, U14.4
BUS_PACK_V+: U4.1, U5.6, U7.1, U8.1, U9.1
MOT_FRONT_OUT_A: J8.1, U7.8
MOT_FRONT_OUT_B: J8.2, U7.9
MOT_REAR_OUT_A: J9.1, U8.8
MOT_REAR_OUT_B: J9.2, U8.9
MOT_STEER_OUT_A: J10.1, U9.8
MOT_STEER_OUT_B: J10.2, U9.9
SIG_FRONT_AIN1: U1.16 (GPIO23/SDIO_CMD), U7.6
SIG_FRONT_AIN2: U1.18 (GPIO24/SDIO_DAT0), U7.7
SIG_FRONT_PWMA: U1.12 (GPIO18/SPI1_~CE0/PCM_CLK/PWM0), U7.5
SIG_FRONT_TACHO_A: J8.3, U1.11 (GPIO17/SPI1_~CE1)
SIG_FRONT_TACHO_B: J8.4, U1.13 (GPIO27/SDIO_DAT3)
SIG_REAR_AIN1: U1.36 (GPIO16/SPI1_~CE2), U8.6
SIG_REAR_AIN2: U1.38 (GPIO20/SPI1_MOSI/PCM_DIN/PWM1), U8.7
SIG_REAR_PWMA: U1.32 (GPIO12/PWM0), U8.5
SIG_REAR_TACHO_A: J9.3, U1.29 (GPCLK1/GPIO05)
SIG_REAR_TACHO_B: J9.4, U1.31 (GPCLK2/GPIO06)
SIG_STEER_AIN1: U1.35 (GPIO19/SPI1_MISO/PCM_FS), U9.6
SIG_STEER_AIN2: U1.37 (GPIO26/SDIO_DAT2), U9.7
SIG_STEER_PWMA: U1.33 (GPIO13/PWM1), U9.5
SIG_STEER_TACHO_A: J10.3, U1.40 (GPIO21/SPI1_SCLK/PCM_DOUT)
SIG_STEER_TACHO_B: J10.4, U1.15 (GPIO22/SDIO_CLK)
SIG_SW_MAIN_IN: SW1.1 (A), U2.5
SIG_SW_MAIN_OUT: SW1.2 (B), U5.5
SIG_TOF1_XSHUT: J1.5, J2.5, J4.5, U1.26 (~CE1_SPI0/GPIO07), U11.5
SIG_TOF2_XSHUT: J1.6, J2.6, J5.5, U1.24 (~CE0_SPI0/GPIO08), U12.5
SIG_TOF3_XSHUT: J1.7, J2.7, J6.5, U1.19 (MOSI_SPI0/GPIO10), U13.5
SIG_TOF4_XSHUT: J1.8, J2.8, J7.5, U1.22 (GPIO25/SDIO_DAT1), U14.5

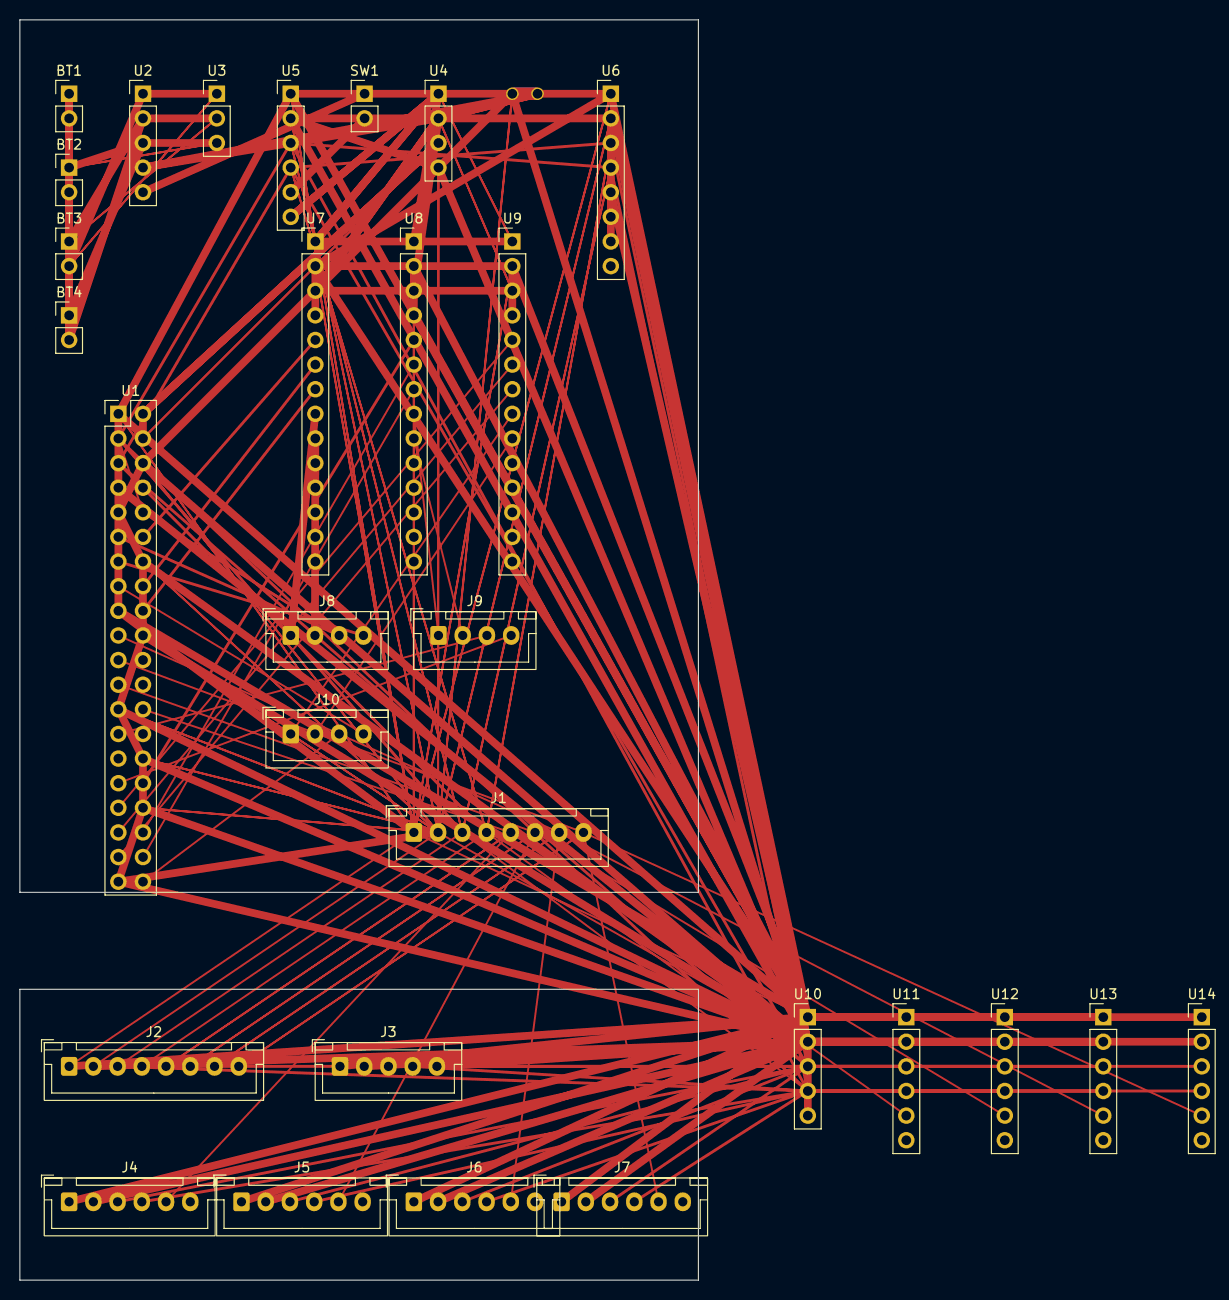
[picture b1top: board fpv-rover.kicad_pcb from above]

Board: 2 copper layers, 70.0 x 130.0 mm, 30 parts (0 on the bottom side), 37 nets.

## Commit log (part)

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2026-06-07 Initial vibe 8)
2026-06-12 Introduce OTA update
2026-06-13 FE: implement RTK
2026-06-13 Set lowercase for repository info
2026-06-13 FE: Update Dockerfile
2026-06-13 FE: Update package-lock.json, Dockerfile
2026-06-13 Introduce bootstrap. Update README
2026-06-13 BE: Update Dockerfile
2026-06-13 Include infra into release
2026-06-13 Bootstrap: resolve "latest" tag
2026-06-14 README: describe interface setup
2026-06-14 nginx: change port
2026-06-14 FE: fix base url
2026-06-14 FE: fix version. Mediamtx: set privileged mode
2026-06-14 ngins: fix
2026-06-14 mediamtx: fix
2026-06-14 docker compose: forward libcamera volume
2026-06-14 Mediamtx: compile custom lib for arducam
2026-06-14 ota / bootstrap: fix race condition
2026-06-14 nginx: update config
2026-06-14 Revert "ota / bootstrap: fix race condition"
    This reverts commit c0114f04dcdd2da18c839d2895b2487cf9cd5f9d.
2026-06-14 Revert "ota / bootstrap: fix race condition"
    This reverts commit 3360c058cca60099089d9dc034b215905ba0af11.
2026-06-14 deploy: implement skip approach for non-changed images
2026-06-14 mediamtx: update dockerfile
2026-06-14 mediamtx: update docker
2026-06-14 docker: specify webrtc host
2026-06-14 mediamtx: specify resolution & bitrate
2026-06-14 fe: update ui. Docker: update version ident
2026-06-14 nginx: fix proxy pass
2026-06-20 FE: fix frontend dev
2026-06-20 FE: refactor & improvements
2026-06-20 VE: fix version check
2026-06-20 OTA scrpipt: add confirmation on manual update
2026-06-20 OTA: fix
2026-06-20 FE: move positioning props to the root level
2026-06-20 FE: add update autocheck, extend event log
2026-06-21 improve ota
2026-06-21 FE: delete css files & refactor to tailwind use
2026-06-21 FE: add app loader
2026-06-21 FE: add badge on new event
2026-06-21 FE: close Settings modal on apply update
2026-06-21 add teardown script
2026-06-21 FE: introduce Select component
2026-06-22 Introduce resolution / bitrate selection
2026-06-22 FE: move constants into file
2026-06-22 bootstrap: check if deploy key exsists
2026-06-27 BE: camera quality-change
2026-06-27 mediamtx: exlude mediamtx.yml from trigger of github action
2026-06-27 github actions: run workflow on unexists previous tag
2026-06-30 Introduce bluetooth module
2026-06-30 bluetooth: fix the closed connection
2026-06-30 release: fix detection of previous version
2026-06-30 Revert "release: fix detection of previous version"
    This reverts commit f1a0110a49166e7500344fa38d0d8a50bc5b527b.
2026-06-30 Revert "release: fix detection of previous version"
    This reverts commit d3f06ad3547cf57b9c45ce67c4b9ee1f0194ab7d.
2026-06-30 bluetooth: forward host network
